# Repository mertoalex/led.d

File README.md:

# led.d
led.d (I just testing myself with making this pcb) <br/>
(this is a KiCad project)

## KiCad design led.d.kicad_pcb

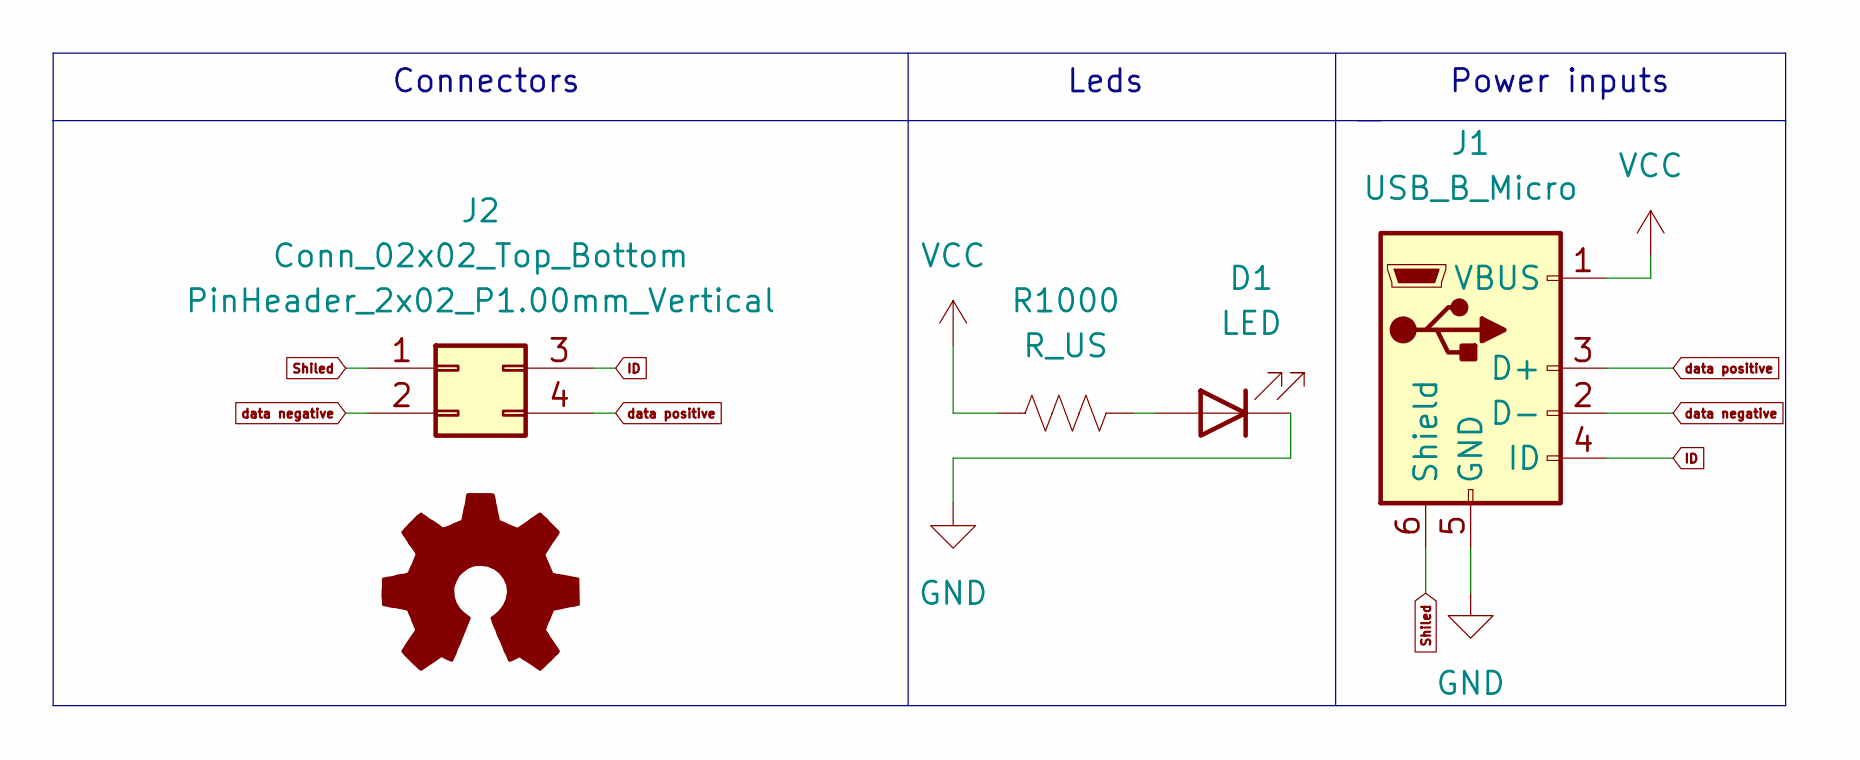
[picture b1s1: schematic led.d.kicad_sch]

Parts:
D1: LED; LED_D5.0mm
J1: USB_B_Micro; USB_Micro-AB_Molex_47590-0001
J2: Conn_02x02_Top_Bottom; PinHeader_2x02_P1.00mm_Vertical
R1000: R_US; R_Axial_DIN0204_L3.6mm_D1.6mm_P5.08mm_Horizontal

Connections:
GND: D1.1 (K), J1.5 (GND)
ID: J1.4 (ID), J2.3
unnamed: D1.2 (A), R1000.2
Shiled: J1.6 (Shield), J2.1
VCC: J1.1 (VBUS), R1000.1
data negative: J1.2 (D-), J2.2
data positive: J1.3 (D+), J2.4

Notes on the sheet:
Connectors
Power inputs
Leds

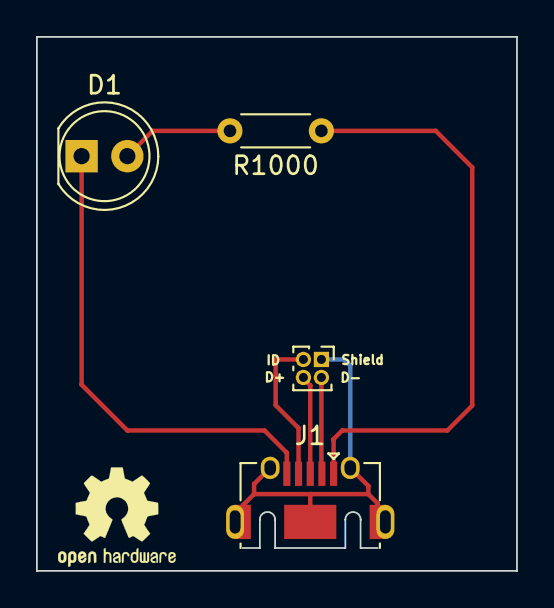
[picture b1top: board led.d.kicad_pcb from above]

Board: 2 copper layers, 26.7 x 29.7 mm, 4 parts (0 on the bottom side), 7 nets.

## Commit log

2022-07-12 first files
2022-07-12 forgor
2022-07-13 gitignore
2022-07-13 I found pinheads
